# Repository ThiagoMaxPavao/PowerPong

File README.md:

# Power Pong

Este repositório contém o projeto final da disciplina Laboratório de Sistemas Embarcados da Unicamp, realizado no segundo semestre de 2024.
O projeto foi originalmente desenvolvido para ser executado em conjunto com a [BitDogLab](https://github.com/BitDogLab/BitDogLab), um projeto educacional do professor Fabiano.

Autores:

- Luciano Cardoso Ferreira Filho
- Thiago Maximo Pavão

Professor: Doutor Fabiano Fruett

## Sobre o Projeto

O projeto consiste na implementação do clássico jogo de fliperama Pong, desenvolvido originalmente pela [Atari](https://pt.wikipedia.org/wiki/Pong), para a plataforma BitDogLab.

O jogo original era controlado por dois controles rotacionais mecânicos (um para cada jogador), e o objetivo era simplesmente rebater a bola para o campo adversário.
No entanto, o objetivo deste projeto foi manter os principais elementos do jogo clássico, ao mesmo tempo em que adicionamos novas mecânicas para aprimorar a jogabilidade.

A principal inovação em hardware é a forma como os jogadores interagem com o jogo. Foi desenvolvida uma luva equipada com LEDs, buzzer, e sensores de acelerômetro e giroscópio.
Além disso, a ponta de cada dedo contém uma fita de cobre para detectar toques entre o polegar e os outros quatro dedos. Atualmente, a luva é destinada ao uso exclusivo da mão
direita, então uma melhoria seria torná-la adaptável para ambas as mãos, ampliando sua acessibilidade.

Em relação ao software, também foram feitas modificações para tornar a jogabilidade mais divertida: os jogadores agora podem usar poderes especiais para alterar o curso da partida,
mas devem utilizá-los de forma estratégica, pois cada poder tem um custo. Além disso, a bola acelera levemente cada vez que um jogador a rebate com seu controle,
tornando o jogo progressivamente mais desafiador. Parte da estratégia no uso dos poderes está relacionada a essa velocidade crescente — alguns poderes se tornam muito mais
eficazes quando usados no momento certo.

## Sobre o Jogo

Este projeto é inspirado no clássico jogo *Pong*, mas com algumas mecânicas inovadoras para torná-lo ainda mais desafiador e interativo. 

### Regras Básicas

- **Objetivo**: O jogador deve defender sua base enquanto tenta ultrapassar a base adversária, movimentando seu pad com os gestos das mãos.
- **Pontuação**: O jogador que conseguir ultrapassar a base do oponente marca 1 ponto. 
- **Cargas**: Após cada ponto, os jogadores recebem "cargas" que podem ser utilizadas para ativar habilidades especiais (detalhadas abaixo).
- **Sets**: A cada 5 pontos acumulados, o jogador vence 1 set. O primeiro a alcançar o número de sets definidos no início do jogo será o vencedor.
- **Desempate**: Caso ambos os jogadores empatem em 4 pontos a 4, entra em vigor a regra "vai a 2": o jogador precisa ganhar dois pontos consecutivos para vencer o set.

### Controles e Configurações

1. **Menu Inicial**: 
   - No início do jogo, é exibido um menu. Pressione o botão **A** para acessar as configurações de número de sets (1, 3 ou 5).
   - Após selecionar o número de sets, os jogadores podem iniciar a partida.

2. **Movimentação dos Pads**:
   - Os pads são controlados pela rotação das mãos.
   - É possível inverter os controles pressionando o dedão contra o dedo médio, permitindo maior personalização para o jogador.

3. **Início do Jogo**:
   - Para começar, ambos os jogadores devem pressionar o dedão contra o dedo indicador simultaneamente. Quando isso acontecer, a bola será lançada e o jogo começará.

### Habilidades Especiais

As cargas acumuladas ao longo da partida podem ser gastas em habilidades estratégicas. Cada habilidade possui um custo específico:

1. **Invisibilidade**  
   - **Custo**: 1 carga  
   - O adversário do jogador que ativar esta habilidade ficará invisível, dificultando a visualização do pad. A invisibilidade dura por 3 rebatidas e pode ser acumulada por ativações consecutivas.

2. **Escudo**  
   - **Custo**: 2 cargas  
   - O jogador ganha um escudo que protege sua base. O escudo dura até a próxima rebatida ou até que o jogador marque um ponto.

3. **Atemporal**  
   - **Custo**: 3 cargas  
   - Reduz a velocidade da bola temporariamente, facilitando sua rebatida. A habilidade dura apenas uma rebatida.

4. **Power Pong**  
   - **Custo**: 4 cargas  
   - Ativa o buff máximo no pad do jogador. Independente do ponto onde a bola atingir o pad, ela será rebatida com a velocidade lateral máxima, tornando difícil para o adversário reagir.

### Limite de Cargas

- A capacidade máxima de cargas é 4.  
- Caso o jogador atinja o limite e tente receber uma carga extra, será alertado por meio do buzzer e LEDs piscando na luva.

## Documentação de Hardware

O projeto de hardware da Luva foi realizado no Kicad, os arquivos podem ser encontrados nesta [pasta](/PCB_Luva).

Os arquivos de produção *.drl* e *.gbr* gerados e utilizados para fabricação desta primeira versão estão disponíveis nesta [pasta](/Fabricação_PCB).

Um diagrama de blocos geral do projeto pode ser visto abaixo

## Componentes utilizados

Os componentes utilizados neste projeto estão organizados em dois grupos: **componentes inclusos no kit da placa BitDogLabs** e **componentes externos**.

### Componentes da BitDogLabs

- **Joystick**  
  Utilizado para selecionar a quantidade de sets (partidas) do jogo.

- **Botão A**  
  Serve para inicializar o jogo e confirmar a quantidade de sets.

- **Buzzer**  
  Emite sons para tornar a partida mais dinâmica, sinalizando colisões com os pads dos jogadores, início e término do jogo, e pontuações.

- **Matriz de LEDs**  
  Exibe a pontuação de cada jogador, o set atual, e os sets vencidos por cada jogador.

- **Display OLED**  
  Indica o set atual e o número total de sets selecionados.

- **Raspberry Pi Pico**  
  Microcontrolador responsável pela programação e controle dos periféricos.

### Componentes Externos

- **Display LCD TFT 128x160**  
  Exibe o jogo, o menu, e as partidas.  
  - [Comprar no Mercado Livre](https://produto.mercadolivre.com.br/MLB-5125731078-modulo-de-tela-lcd-tft-de-18-128x160-spi-color-st7735-_JM)

- **1x2 (1 por luva) Expansores IO I2C (PCF8575)**  
  Expandem a porta I2C para conectar os botões de habilidades, LEDs de sinalização de carga de poder, buzzer de alerta de carga cheia e LED RGB para identificar o jogador.  
  - [Comprar no Aliexpress](https://pt.aliexpress.com/item/1005007080964232.html)

- **1x2 (1 por luva) MPU-6050**  
  Sensores utilizados para controlar os pads de cada jogador através da rotação da mão.  
  - [Comprar no Mercado Livre](https://produto.mercadolivre.com.br/MLB-1922679879-modulo-mpu6050-gy-521-sensor-acelermetro-giroscopio-3-eixos-_JM)

- **7x2 (7 por luva) Resistores de 200Ω**  
  Controlam a intensidade da luz dos LEDs de carga e protegem o LED RGB contra sobrecorrente.  
  - [Comprar no Mercado Livre](https://produto.mercadolivre.com.br/MLB-1624979305-resistor-200-ohm-5-10pecas-_JM)

- **4x2 (4 por luva) Resistores de 5kΩ (ou valor próximo)**  
  Usados como lógica pull-down para os botões de habilidades.
  - [Comprar no Mercado Livre](https://produto.mercadolivre.com.br/MLB-1722095500-kit-10-x-resistor-47k-ohm-14w-5-projeto-arduino-raspberry-_JM?matt_tool=14213447&matt_word=&matt_source=bing&matt_campaign=MLB_ML_BING_AO_CE-ALL-ALL_X_PLA_ALLB_TXS_ALL&matt_campaign_id=382858295&matt_ad_group=CE&matt_match_type=e&matt_network=o&matt_device=c&matt_keyword=default&msclkid=34bebad5f9b4163fa580dd9956da3a71&utm_source=bing&utm_medium=cpc&utm_campaign=MLB_ML_BING_AO_CE-ALL-ALL_X_PLA_ALLB_TXS_ALL&utm_term=4581596253419739&utm_content=CE)

- **4x2 (4 por luva) LEDs (brancos ou azuis)**  
  Indicadores de carga de poder armazenada.  
  - [Comprar no Mercado Livre](https://produto.mercadolivre.com.br/MLB-2015068823-50x-led-5mm-azul-difuso-_JM)

- **1x2 (1 por luva) Buzzer Passivo 5V**  
  Sinaliza que as cargas de poder estão cheias.  
  - [Comprar no Mercado Livre](https://produto.mercadolivre.com.br/MLB-2664375798-buzzer-passivo-5v-continuo-arduino-raspberry-pic-arm-_JM)

- **1x2 (1 por luva) LED RGB (ânodo comum)**  
  Identifica o jogador através da cor do pad.  
  - [Comprar no Mercado Livre](https://produto.mercadolivre.com.br/MLB-3914705318-kit-10-leds-rgb-5mm-nodo-comum-_JM)

## Esquemático do Circuito da Luva

O esquemático do circuito da luva foi dividido em partes para facilitar o entendimento de cada seção do projeto.

### Conexões Principais

Nesta parte do esquemático, são exibidas as conexões entre o **PCF8575**, **MPU6050** e o soquete que conecta a placa desenvolvida com a **BitDogLab**. Ambos os componentes estão conectados à mesma porta **I2C**. Como a BitDogLab possui duas portas I2C disponíveis, cada porta será utilizada por um jogador.

- **PCF8575**: Recebe alimentação pelo pino **VCC** e fornece saída pelo **VDD**. Como a alimentação é de 3.3V, é necessário realizar um curto entre **VCC** e **VDD** na parte traseira da placa para garantir a mesma tensão em ambos. Isso permite alimentar outros componentes pelo VDD.
- As portas do **PCF8575** estão conectadas a diversos periféricos, como botões, LEDs, LED RGB e buzzer.

### Lógica dos Botões

Nesta seção, é apresentada a lógica para os botões:

- **D1 (polegar)**: Conectado ao **VDD**, com tensão de 3.3V.
- **D2, D3, D4 e D5 (outros dedos)**: Conectados a resistores de 5kΩ configurados em uma lógica **Pull-Down**, ligados ao **GND**.

Quando o dedão toca outro dedo, o circuito se fecha, funcionando de maneira similar ao pressionar um botão. O nível lógico resultante é lido pelas portas do **PCF8575**.

### LEDs Indicadores de Carga

Esta parte do circuito controla os LEDs que indicam a quantidade de carga:

- Os LEDs estão conectados ao **VDD** e ao **GND** através das portas do **PCF8575**.
- Como o **PCF8575** não fornece corrente suficiente para acionar os LEDs diretamente quando configurado como saída de **VDD**, foi utilizada a ligação mostrada no esquemático, permitindo o funcionamento correto.

### LED RGB e Buzzer

Nesta seção, são apresentados o LED RGB e o Buzzer:

- **LED RGB**: Utiliza um **ânodo comum**, o que permite funcionar corretamente com a lógica de alimentação similar à dos LEDs de carga.
- **Buzzer**: Conectado de maneira similar para superar a limitação de corrente mencionada.

## Projeto da Placa de Circuito Impresso (PCB)

A seguir, temos a imagem do layout da PCB desenvolvida:

### Organização dos Componentes

- **MPU6050** e **PCF8575**: Posicionados próximos ao soquete para facilitar as conexões.
- **LEDs de carga**: Alinhados próximos ao Buzzer, na ordem em que serão acionados.
- **LED RGB**: Localizado no lado direito da placa, identificando o jogador.
- **Fios para os dedos**: Organizados para se alinhar corretamente à luva, facilitando a conexão.
- **Furos de fixação**: Incluídos para prender a placa na luva, garantindo estabilidade.

O design priorizou uma PCB de face simples, otimizando o posicionamento dos componentes e minimizando o uso de trilhas cruzadas.

## Conexões

A conexão da placa desenvolvida foi feita através 2 cabos de 4 vias com conector JST conectados entre si conectada na entrada I2C da BitDogLab.

Outra conexão importante foi realizada com o LCD, seguindo o esquema de ligação descrito no repositório [pico-1p54in-lcd-graphics](https://github.com/BitDogLab/BitDogLab/tree/main/softwares/pico-1p54in-lcd-graphics). 

Para facilitar e tornar mais estável essa conexão, o professor **Fabiano Fruett** desenvolveu um **shield** específico para o LCD, que foi utilizado na etapa final do projeto.

- IMPORTANTE!!
  É necessário realizar um curto de solda entre os terminais de VCC e VDD presentes na parte de baixo do módulo PCF8575, como mostrado na Figura abaixo. Desta forma a alimentação do módulo é repassada para os pinos IO.

## Construção mecânica

A PCB foi impressa pela FEEC através do SATE.

Após obter a placa foram soldados os componentes.

Com a placa pronta, foi utilizada uma luva lã como suporte e para o jogador poder vestir e jogar, através dos furos colocados anteriormente a placa foi costurada à luva.

Para a conexão nos dedos e utilizados como botões foram soldados jumpers com esta finalidade em uma fita de cobre que se enrolava nas pontas dos dedos.

Após ser montado duas luvas para dois jogadores, as luvas foram conectas as placa BitDogLab através de 2 cabos de 4 vias com conector JST conectados entre si, como dito anteriormente, com o intutio de ter maior mobilidade para o jogador, além disto a conexão com o LCD com a BitDogLab foi feita através de um shield desenvolvido pelo Professor Fabiano Fruett.

## Documentação de Software

O software foi desenvolvido em MicroPython, utilizando algumas bibliotecas escritas em Python, que estão inclusas neste repositório.

Além dessas bibliotecas em Python, uma biblioteca escrita em C foi incorporada ao firmware da placa para interagir com o display. Essa abordagem foi necessária devido ao alto volume de dados trocados com o display, que tornava uma solução em Python ineficiente.

A biblioteca utilizada para essa interação foi [st7789_mpy](https://github.com/russhughes/st7789_mpy). Contudo, ao utilizar o firmware disponibilizado no repositório original, encontramos erros que acreditamos serem causados pela incompatibilidade entre a versão do MicroPython usada e aquela com a qual o firmware foi compilado.

Para resolver o problema, geramos um firmware com a última versão estável do MicroPython disponível (v1.24), incluindo a biblioteca necessária. Esse firmware está disponível na raiz do repositório, no arquivo firmware.uf2. O processo de geração foi baseado em uma solução detalhada em uma issue do repositório da biblioteca. Você pode consultar a explicação [aqui](https://github.com/russhughes/st7789_mpy/issues/168#issuecomment-2342353619). O procedimento funcionou corretamente.

### Máquina de Estados

O fluxo do programa é baseado em uma máquina de estados, representada na figura abaixo:

Cada estado executa as seguintes tarefas:

MENU: Exibe o nome do jogo e as instruções iniciais piscando. O programa aguarda que o botão A seja pressionado para avançar ao próximo estado.

CHOOSE SETS: Mostra na tela as opções de quantidade de sets (melhor de 1, 3 ou 5). O joystick horizontal é usado para alternar entre as opções. Pressionar o botão A confirma a escolha e avança para o próximo estado.

GAME BREAK: Aguarda ambos os jogadores pressionarem seus botões simultaneamente, indicando que estão prontos para começar a partida.

GAME RUNNING: Atualiza a posição dos pads dos jogadores com base nos dados do acelerômetro, verifica o uso do poder de escudo e simula a física da bolinha, incluindo colisões com as paredes e pads.

END: Mostra uma animação, toca a música de vitória e exibe na tela o nome do jogador vencedor.

### Lógica do Sensor

O sensor retorna valores de aceleração em três eixos, mas apenas dois são utilizados para calcular o ângulo de inclinação do dispositivo, como ilustrado abaixo:

Devido a flutuações nas leituras do sensor, aplicamos um filtro digital passa-baixas para suavizar os valores do ângulo. Este filtro também compensa descontinuidades angulares (como a transição de -π para π). Após o processamento, os valores são escalados para representar a posição vertical do pad na tela. Essa conversão associa um intervalo de -45° a 45° aos limites da tela, que vão de PAD_WIDTH//2 até WIDTH - PAD_WIDTH//2, onde WIDTH é a largura da tela e PAD_WIDTH é a largura do pad.

Por fim, garantimos que a posição do pad permaneça dentro dos limites da tela. O processo é ilustrado na figura abaixo:

### Velocidade da Bolinha

A velocidade da bolinha aumenta gradualmente a cada rebote, tornando o jogo mais dinâmico. No início de cada round, a velocidade inicial é ajustada com base no desempenho dos jogadores. Após cada round, a bolinha perde 30% de sua velocidade final, equilibrando o ritmo do jogo para que a bola não fique nem muito lenta nem muito rápida.

### Organização dos Arquivos

Os arquivos que compõe a memória da Raspberry Pi Pico, necessários para executar o jogo são os mostrados abaixo, e estão disponíveis nesta [pasta](/code).

1. Lógica principal do programa
    - *main.py*: Inicialização e execução da máquina de estados.

2. Lógica de jogo
    - *game_classes.py*: Classes da lógica de Jogo, como a classe de jogador, da bola e do escudo.
    - *game_constants.py*: Valores constantes como tamanhos dos jogadores, dimensões da tela e outros.
    - *game_routines.py*: Rotinas de execução de cada estado da máquina de estados. Responsável por orquestrar os objetos definidos a depender do estado corrente.

3. Periféricos
    - *mpu6050.py*: Biblioteca para interação com o MPU6050, sensor I2C acelerômetro e giroscópio de 6 eixos.
    - *pcf8575.py*: Biblioteca para interação com o PCF8575, extensor de I/O I2C com diversas portas GPIO.
    - *ssd1306.py*: Biblioteca para interação com o SSD1306, display OLED I2C 128x64px.
    - *tft_config.py*: Arquivo de configuração do display LCD SPI utilizado, definindo a equivalência das portas do display com as da Raspberry.
    - *glove.py*: Biblioteca criada para facilitar interação com os componentes presentes na luva, oferencendo acesso direto ao valor do ângulo em que a luva está posicionada e aos periféricos conectados ao extensor de I/O. Também executa uma rotina de testes na luva se executado diretamente.
    - *peripherals.py*: Classe de incialização de todos os periféricos controlados pelo projeto, também carrega uma referência a cada um deles para evitar a necessidade de passagem de muitos parâmetros para as rotinas do jogo.

4. Funções auxiliares
    - *util.py*

5. Fontes para escrita no display LCD
    - *vga1_16x32.py*
    - *vga1_8x8.py*
    - *vga1_bold_16x32.py*

## Resultados

O projeto foi concluído com sucesso e proporcionou um grande aprendizado para a equipe. Como o projeto é um jogo, nos divertimos muito durante o desenvolvimento, especialmente ao imaginar a dinâmica e a diversão que os jogadores teriam. Utilizamos nossa criatividade para projetar os comandos do controle, os poderes e as interações do jogo.

### Desafios Enfrentados

Durante o desenvolvimento, enfrentamos alguns desafios importantes que contribuíram para a melhoria contínua do projeto:

- **Substituição do Display**: No início, o display originalmente escolhido teve que ser substituído, o que exigiu ajustes significativos no código. Embora isso tenha demandado tempo, essa experiência nos ajudou a modularizar o código, facilitando futuras alterações e melhorias.
  
- **Atrasos na Produção da Placa**: O processo de impressão da placa sofreu atrasos, o que impediu a realização de testes e afetou o desenvolvimento de funcionalidades adicionais, como novas utilidades para o LED RGB e o buzzer.

### Melhorias Futuras

Identificamos diversas áreas para melhorar o projeto em versões futuras:

#### 1. **Hardware**
   - **Redução do Tamanho da Placa**: A placa pode ser compactada, eliminando o uso de módulos como o PCF8575 e o MPU6050 e substituindo-os por componentes individuais.
   - **Uso de Componentes SMD**: A utilização de componentes SMD (Surface-Mounted Device) ajudará a reduzir ainda mais o tamanho da placa.
   - **Conforto para o Jogador**: Melhorar o material e o método de fixação da luva, garantindo maior conforto ao jogador durante o uso.
   
#### 2. **Funcionalidades**
   - **Uso das Portas Disponíveis**: Aproveitar as portas restantes do PCF8575 para adicionar mais LEDs para indicar níveis de carga ou novos poderes.
   - **Otimização do Código**: Reescrever o código em C para melhorar a eficiência e tornar o jogo mais dinâmico.

Essas melhorias visam tornar o projeto mais eficiente, compacto e com maior interatividade para o usuário.

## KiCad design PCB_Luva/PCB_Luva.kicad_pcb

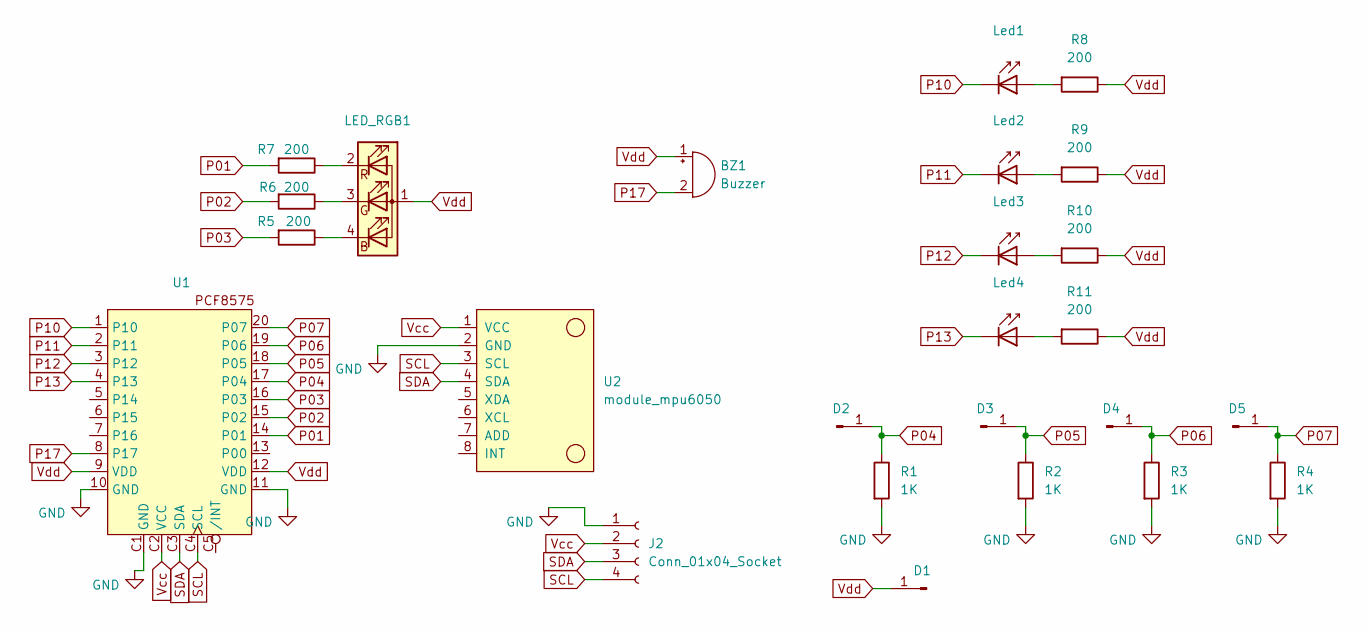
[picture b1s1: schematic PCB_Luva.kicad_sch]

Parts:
BZ1: Buzzer; Buzzer_D14mm_H7mm_P10mm
D1, D2, D3, D4, D5: Conn_01x01_Pin; PinHeader_1x01_P2.54mm_Vertical
J2: Conn_01x04_Socket; JST_XH_B4B-XH-A_1x04_P2.50mm_Vertical
LED_RGB1: LED_ARGB; LED_D5.0mm-4_RGB
Led1, Led2, Led3, Led4: LD274; LED_D5.0mm_IRGrey
R1, R2, R3, R4: 1K; R_Axial_DIN0207_L6.3mm_D2.5mm_P10.16mm_Horizontal
R5, R6, R7, R8, R9, R10, R11: 200; R_Axial_DIN0207_L6.3mm_D2.5mm_P10.16mm_Horizontal
U1: 16-bit IO Expander
U2: module_mpu6050

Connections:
GND: J2.1, R1.2, R2.2, R3.2, R4.2, U1.10 (GND), U1.11 (GND), U1.C1 (GND), U2.2 (GND)
unnamed: LED_RGB1.4 (BK), R5.1
unnamed: LED_RGB1.3 (GK), R6.1
unnamed: LED_RGB1.2 (RK), R7.1
unnamed: Led1.2 (A), R8.2
unnamed: Led2.2 (A), R9.2
unnamed: Led3.2 (A), R10.2
unnamed: Led4.2 (A), R11.2
P01: R7.2, U1.14 (P01)
P02: R6.2, U1.15 (P02)
P03: R5.2, U1.16 (P03)
P04: D2.1, R1.1, U1.17 (P04)
P05: D3.1, R2.1, U1.18 (P05)
P06: D4.1, R3.1, U1.19 (P06)
P07: D5.1, R4.1, U1.20 (P07)
P10: Led1.1 (K), U1.1 (P10)
P11: Led2.1 (K), U1.2 (P11)
P12: Led3.1 (K), U1.3 (P12)
P13: Led4.1 (K), U1.4 (P13)
P17: BZ1.2 (-), U1.8 (P17)
SCL: J2.4, U1.C4 (SCL), U2.3 (SCL)
SDA: J2.3, U1.C3 (SDA), U2.4 (SDA)
Vcc: J2.2, U1.C2 (VCC), U2.1 (VCC)
Vdd: BZ1.1 (+), D1.1, LED_RGB1.1 (A), R8.1, R9.1, R10.1, R11.1, U1.9 (VDD), U1.12 (VDD)

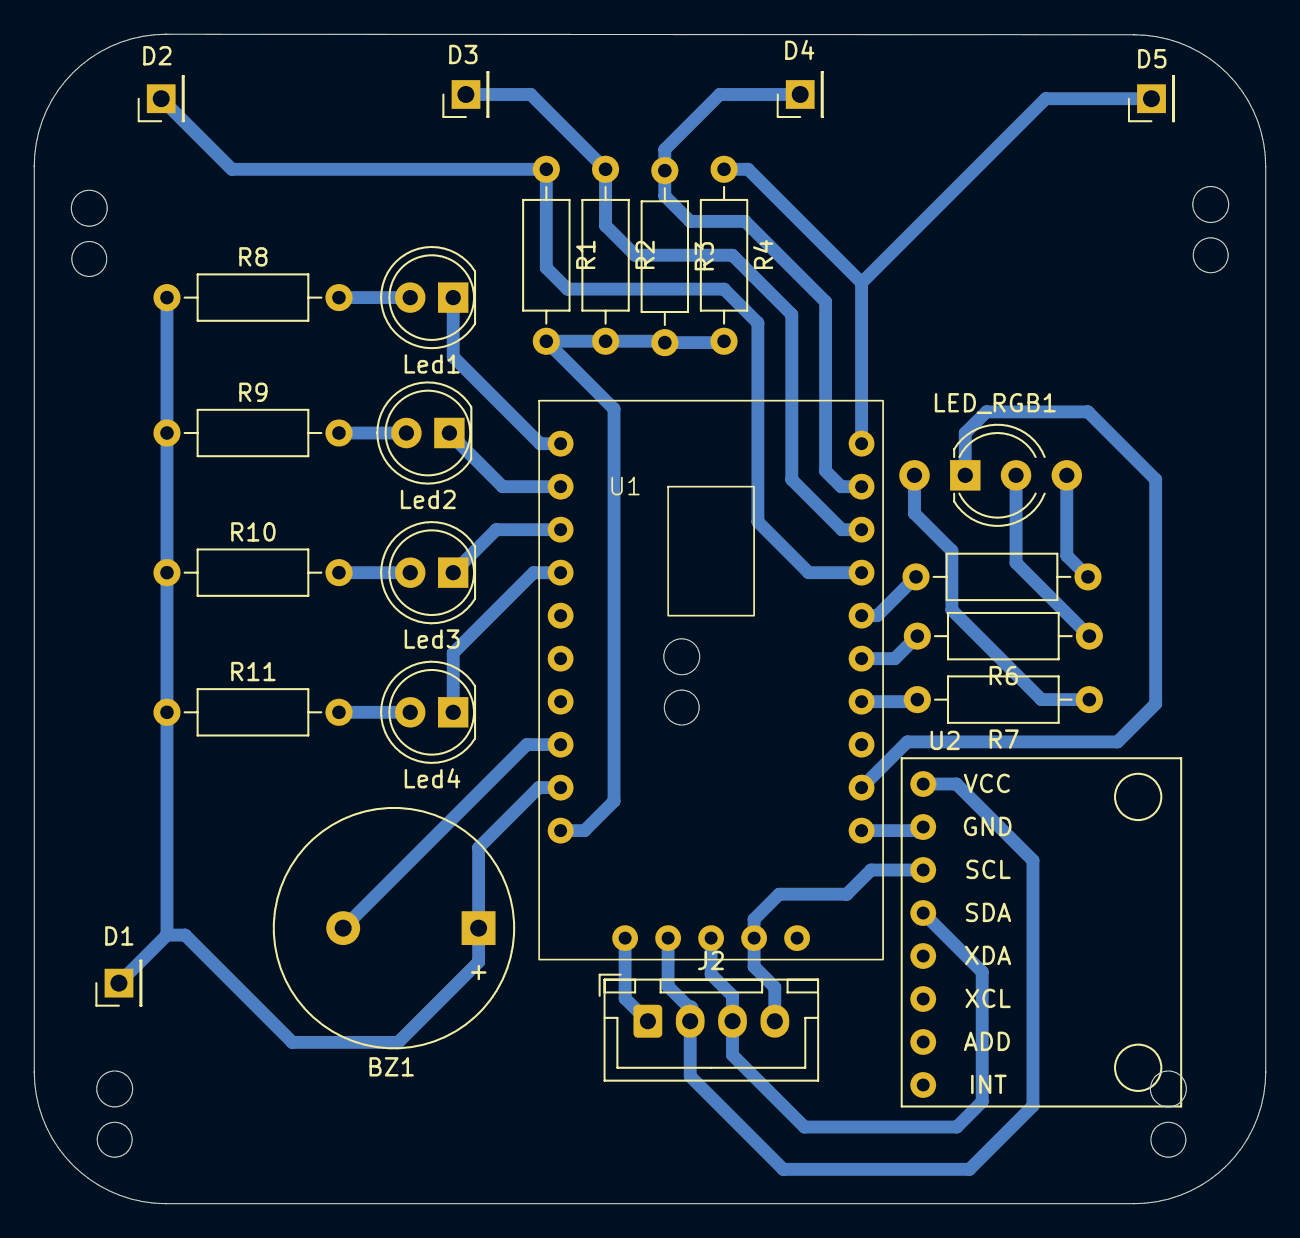
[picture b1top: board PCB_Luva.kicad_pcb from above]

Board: 2 copper layers, 72.8 x 69.1 mm, 25 parts (0 on the bottom side), 24 nets.

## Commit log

2024-11-15 init
2024-11-15 first download
2024-11-15 fix fonts
2024-11-15 fix choose_sets_routine
2024-11-16 game break state fix
2024-11-16 new hardware fix done
2024-11-23 ajuste no calculo angulo
2024-11-23 update shield
2024-11-23 logica de poderes
2024-11-23 inicialização reinicia todos os periféricos
2024-11-23 poder de invisibilidade
2024-11-23 debouce por software nos botoes da luva
2024-11-23 atualizacao na logica de poderes agora o poder pode informar que nao conseguiu ser utilizado, impedindo que pontos sejam gastos desncessariamente
2024-11-23 poder buffed pad
2024-11-23 habilidade time shield e co no led rgb da luva
2024-11-24 logica de invert controls proposital
2024-11-28 move to code folder
2024-11-28 estruturacao documentacao de software
2024-11-28 documentacao de software
2024-11-28 firmware e explicação
2024-11-28 Imagens documentacao de software
2024-11-28 ajustes no texto
2024-11-29 Organizacao dos arquivos
2024-12-01 upload projeto kicad e arquivos de fabricação
2024-12-01 ajustes ao texto
2024-12-01 Diagrama de blocos geral
